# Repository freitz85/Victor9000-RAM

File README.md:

# Victor9000-RAM

The Victor9000-RAM is a modern RAM expansion card for the Victor 9000 computer that extends RAM to the maximum 896k and additionally provides a battery-backed-up real-time clock.

Jumper JP1 open is for use on a 256k motherboard, and JP1 closed is for a 128k motherboard.

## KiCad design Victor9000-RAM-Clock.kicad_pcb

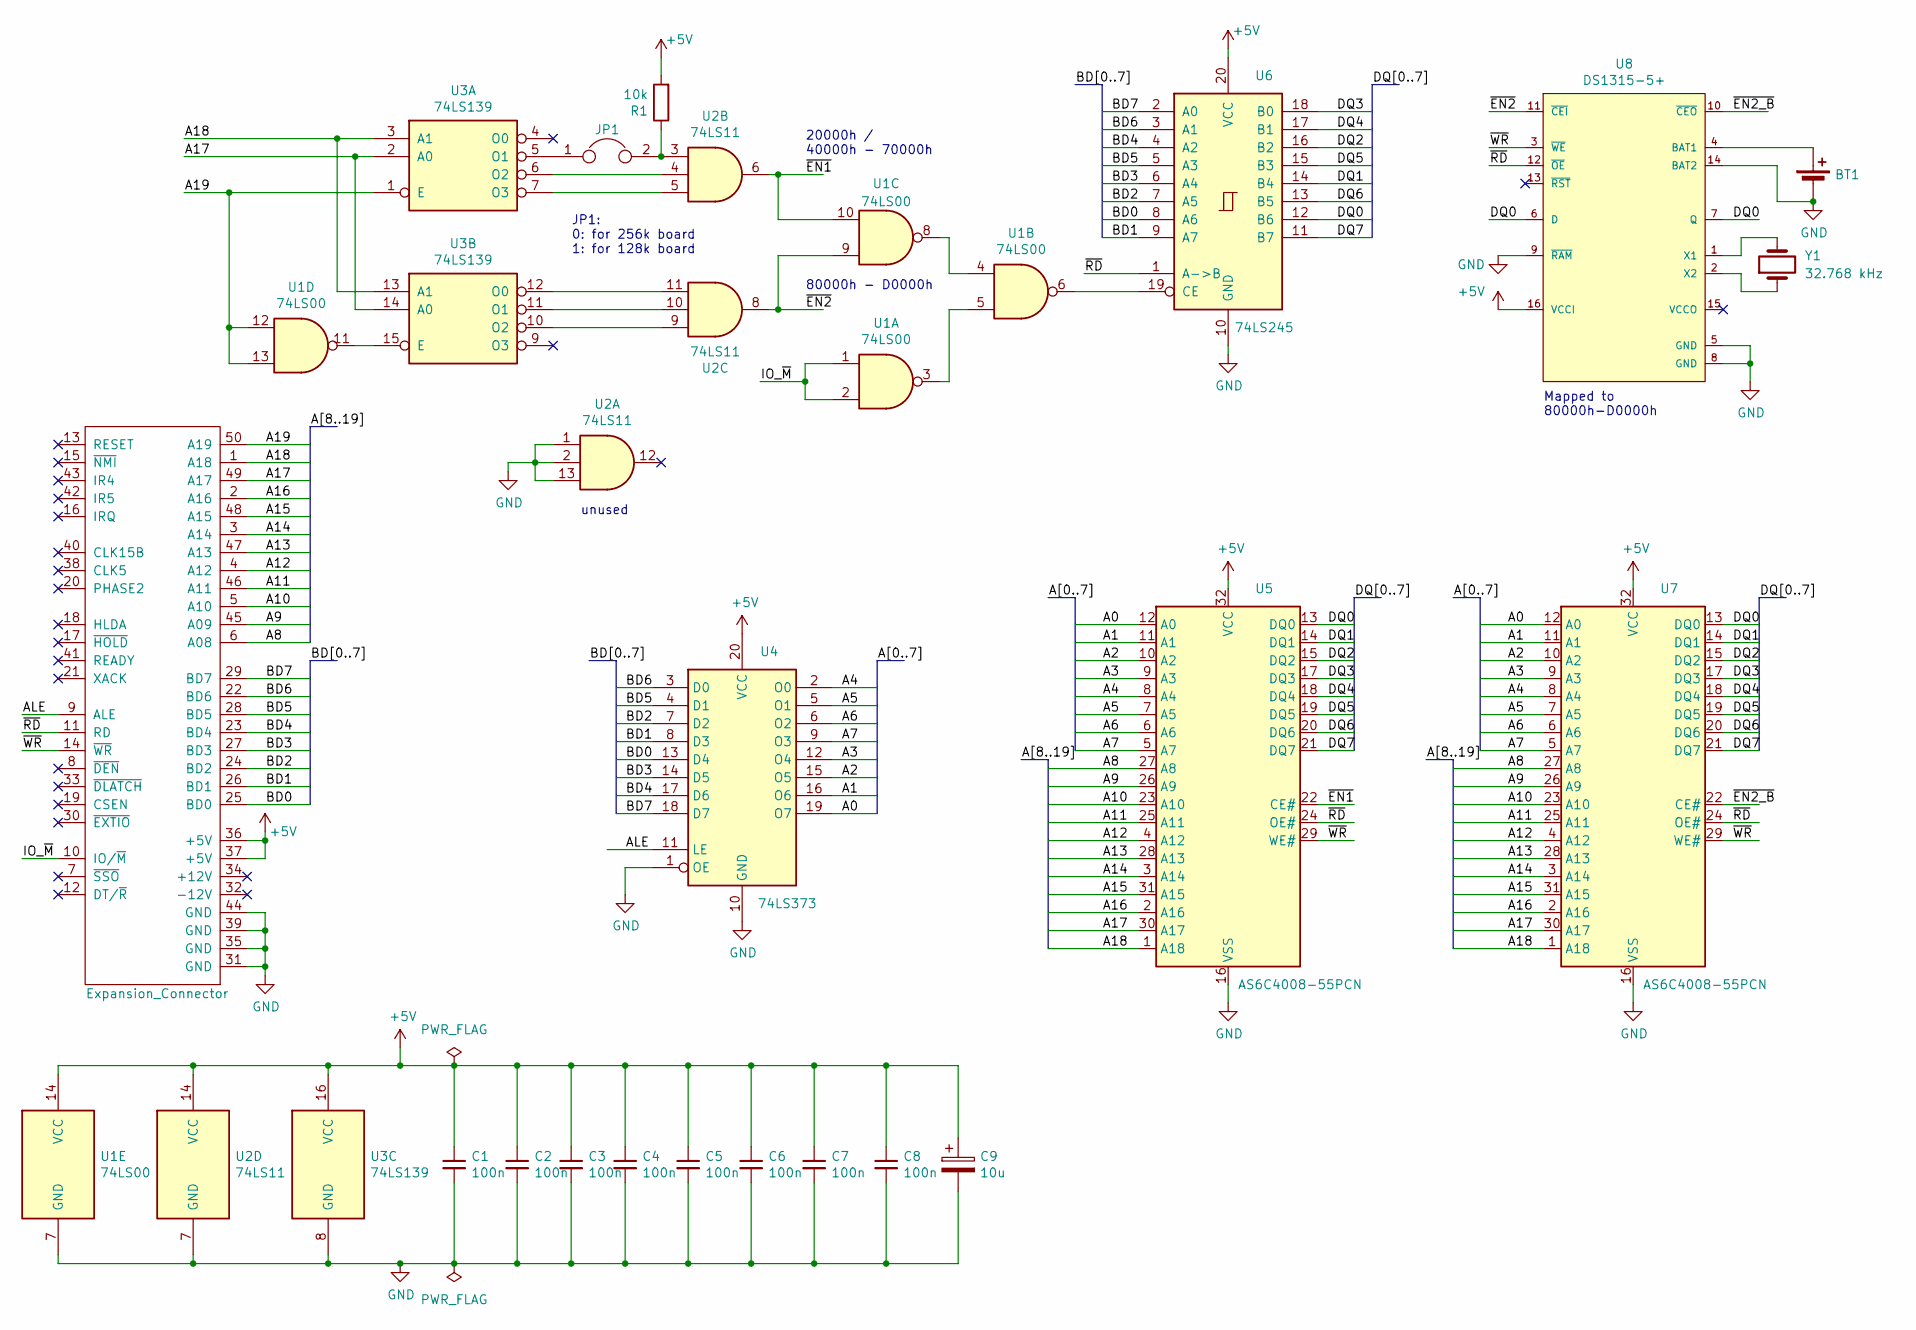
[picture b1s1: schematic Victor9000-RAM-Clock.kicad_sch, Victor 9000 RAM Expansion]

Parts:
BT1: Battery_Cell; BatteryHolder_Keystone_103_1x20mm
C1, C2, C3, C4, C5, C6, C7, C8: 100n; C_Disc_D5.0mm_W2.5mm_P2.50mm
C9: 10u; CP_Radial_D6.3mm_P2.50mm
H1: Expansion_Connector; Victor Expansion Edge Connector
JP1: Jumper; PinHeader_1x02_P2.54mm_Vertical
R1: 10k; R_Axial_DIN0207_L6.3mm_D2.5mm_P7.62mm_Horizontal
U1: 74LS00; DIP-14_W7.62mm
U2: 74LS11; DIP-14_W7.62mm
U3: 74LS139; DIP-16_W7.62mm
U4: 74LS373; DIP-20_W7.62mm
U5, U7: AS6C4008-55PCN; DIP-32_W15.24mm
U6: 74LS245; DIP-20_W7.62mm
U8: DS1315-5+; Maxim-DS1315-5+-Manufacturer_Recommended
Y1: 32.768 kHz; Crystal_DS26_D2.0mm_L6.0mm_Horizontal

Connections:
+5V: C1.1, C2.1, C3.1, C4.1, C5.1, C6.1, C7.1, C8.1, C9.1, H1.36 (+5V), H1.37 (+5V), R1.2, U1.14 (VCC), U2.14 (VCC), U3.16 (VCC), U4.20 (VCC), U5.32 (VCC), U6.20 (VCC), U7.32 (VCC), U8.16 (VCCI)
/A0: U4.19 (O7), U5.12 (A0), U7.12 (A0)
/A1: U4.16 (O6), U5.11 (A1), U7.11 (A1)
/A2: U4.15 (O5), U5.10 (A2), U7.10 (A2)
/A3: U4.12 (O4), U5.9 (A3), U7.9 (A3)
/A4: U4.2 (O0), U5.8 (A4), U7.8 (A4)
/A5: U4.5 (O1), U5.7 (A5), U7.7 (A5)
/A6: U4.6 (O2), U5.6 (A6), U7.6 (A6)
/A7: U4.9 (O3), U5.5 (A7), U7.5 (A7)
/A8: H1.6 (A08), U5.27 (A8), U7.27 (A8)
/A9: H1.45 (A09), U5.26 (A9), U7.26 (A9)
/A10: H1.5 (A10), U5.23 (A10), U7.23 (A10)
/A11: H1.46 (A11), U5.25 (A11), U7.25 (A11)
/A12: H1.4 (A12), U5.4 (A12), U7.4 (A12)
/A13: H1.47 (A13), U5.28 (A13), U7.28 (A13)
/A14: H1.3 (A14), U5.3 (A14), U7.3 (A14)
/A15: H1.48 (A15), U5.31 (A15), U7.31 (A15)
/A16: H1.2 (A16), U5.2 (A16), U7.2 (A16)
/A17: H1.49 (A17), U3.2 (A0), U3.14 (A0), U5.30 (A17), U7.30 (A17)
/A18: H1.1 (A18), U3.3 (A1), U3.13 (A1), U5.1 (A18), U7.1 (A18)
/A19: H1.50 (A19), U1.12, U1.13, U3.1 (E)
/ALE: H1.9 (ALE), U4.11 (LE)
/BD0: H1.25 (BD0), U4.13 (D4), U6.8 (A6)
/BD1: H1.26 (BD1), U4.8 (D3), U6.9 (A7)
/BD2: H1.24 (BD2), U4.7 (D2), U6.7 (A5)
/BD3: H1.27 (BD3), U4.14 (D5), U6.6 (A4)
/BD4: H1.23 (BD4), U4.17 (D6), U6.4 (A2)
/BD5: H1.28 (BD5), U4.4 (D1), U6.5 (A3)
/BD6: H1.22 (BD6), U4.3 (D0), U6.3 (A1)
/BD7: H1.29 (BD7), U4.18 (D7), U6.2 (A0)
/DQ0: U5.13 (DQ0), U6.12 (B6), U7.13 (DQ0), U8.6 (D), U8.7 (Q)
/DQ1: U5.14 (DQ1), U6.14 (B4), U7.14 (DQ1)
/DQ2: U5.15 (DQ2), U6.16 (B2), U7.15 (DQ2)
/DQ3: U5.17 (DQ3), U6.18 (B0), U7.17 (DQ3)
/DQ4: U5.18 (DQ4), U6.17 (B1), U7.18 (DQ4)
/DQ5: U5.19 (DQ5), U6.15 (B3), U7.19 (DQ5)
/DQ6: U5.20 (DQ6), U6.13 (B5), U7.20 (DQ6)
/DQ7: U5.21 (DQ7), U6.11 (B7), U7.21 (DQ7)
/IO_~M: H1.10 (IO/~M), U1.1, U1.2
/~EN1: U1.10, U2.6, U5.22 (CE#)
/~EN2_B: U7.22 (CE#), U8.10 (~CEO)
/~EN2: U1.9, U2.8, U8.11 (~CEI)
/~RD: H1.11 (RD), U5.24 (OE#), U6.1 (A->B), U7.24 (OE#), U8.12 (~OE)
/~WR: H1.14 (~WR), U5.29 (WE#), U7.29 (WE#), U8.3 (~WE)
GND: BT1.2 (-), C1.2, C2.2, C3.2, C4.2, C5.2, C6.2, C7.2, C8.2, C9.2, H1.31 (GND), H1.35 (GND), H1.39 (GND), H1.44 (GND), U1.7 (GND), U2.1, U2.2, U2.7 (GND), U2.13, U3.8 (GND), U4.1 (OE), U4.10 (GND), U5.16 (VSS), U6.10 (GND), U7.16 (VSS), U8.5 (GND), U8.8 (GND), U8.9 (~RAM), U8.14 (BAT2)
unnamed: BT1.1 (+), U8.4 (BAT1)
unnamed: JP1.2, R1.1, U2.3
unnamed: U1.3, U1.5
unnamed: U1.4, U1.8
unnamed: JP1.1, U3.5 (O1)
unnamed: U2.4, U3.6 (O2)
unnamed: U2.5, U3.7 (O3)
unnamed: U1.11, U3.15 (E)
unnamed: U2.11, U3.12 (O0)
unnamed: U2.10, U3.11 (O1)
unnamed: U2.9, U3.10 (O2)
unnamed: U1.6, U6.19 (CE)
unnamed: U8.1 (X1), Y1.2
unnamed: U8.2 (X2), Y1.1

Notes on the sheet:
unused
80000h - D0000h
JP1: 0: for 256k board 1: for 128k board
20000h / 40000h - 70000h
Mapped to 80000h-D0000h

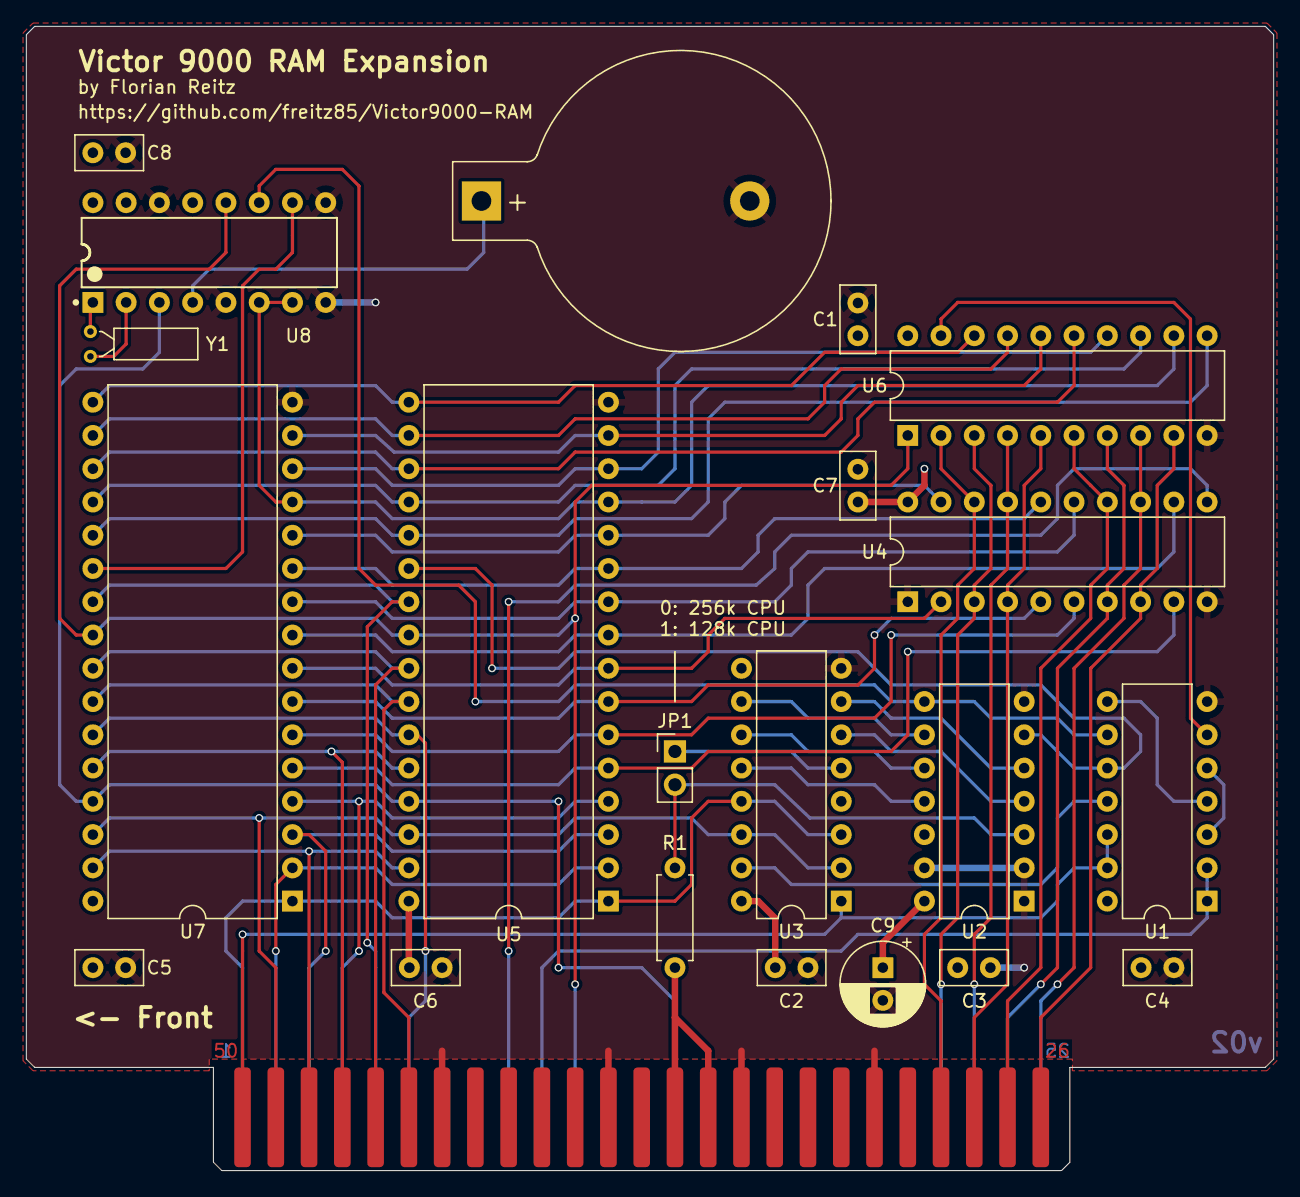
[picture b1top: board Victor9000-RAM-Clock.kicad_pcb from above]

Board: 2 copper layers, 95.2 x 87.4 mm, 22 parts (0 on the bottom side), 59 nets.

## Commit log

2021-12-08 Files added
2021-12-09 Layout
2021-12-12 Routing completed
2021-12-12 DS1315 added
2021-12-12 Comments added
2021-12-17 Swapped layers
2021-12-21 Wavedrom file added
2024-05-07 Crystal added
2025-04-15 Read and write access corrected
